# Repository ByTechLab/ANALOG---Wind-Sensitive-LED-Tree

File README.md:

<div align="center">
    
</div>

Wind sensitive LED tree project (analog circuit).

### Read more at BYTECHLAB:

<table style="width: 100%; border: none;" cellspacing="0" cellpadding="0" border="0">
  <tr>
    <td></td>
    <td>https://bytechlab.com/2019/02/led-tree/</td>
  </tr>
</table>

## License
Software \ Firmware:

Hardware \ Hardware design files \ Hardware documentation:

[![CC BY-NC-SA 4.0][cc-by-nc-sa-shield]][cc-by-nc-sa]

[Creative Commons Attribution-NonCommercial-ShareAlike 4.0 International License][cc-by-nc-sa].

[![CC BY-NC-SA 4.0][cc-by-nc-sa-image]][cc-by-nc-sa]

[cc-by-nc-sa]: http://creativecommons.org/licenses/by-nc-sa/4.0/
[cc-by-nc-sa-image]: https://licensebuttons.net/l/by-nc-sa/4.0/88x31.png
[cc-by-nc-sa-shield]: https://img.shields.io/badge/License-CC%20BY--NC--SA%204.0-lightgrey.svg

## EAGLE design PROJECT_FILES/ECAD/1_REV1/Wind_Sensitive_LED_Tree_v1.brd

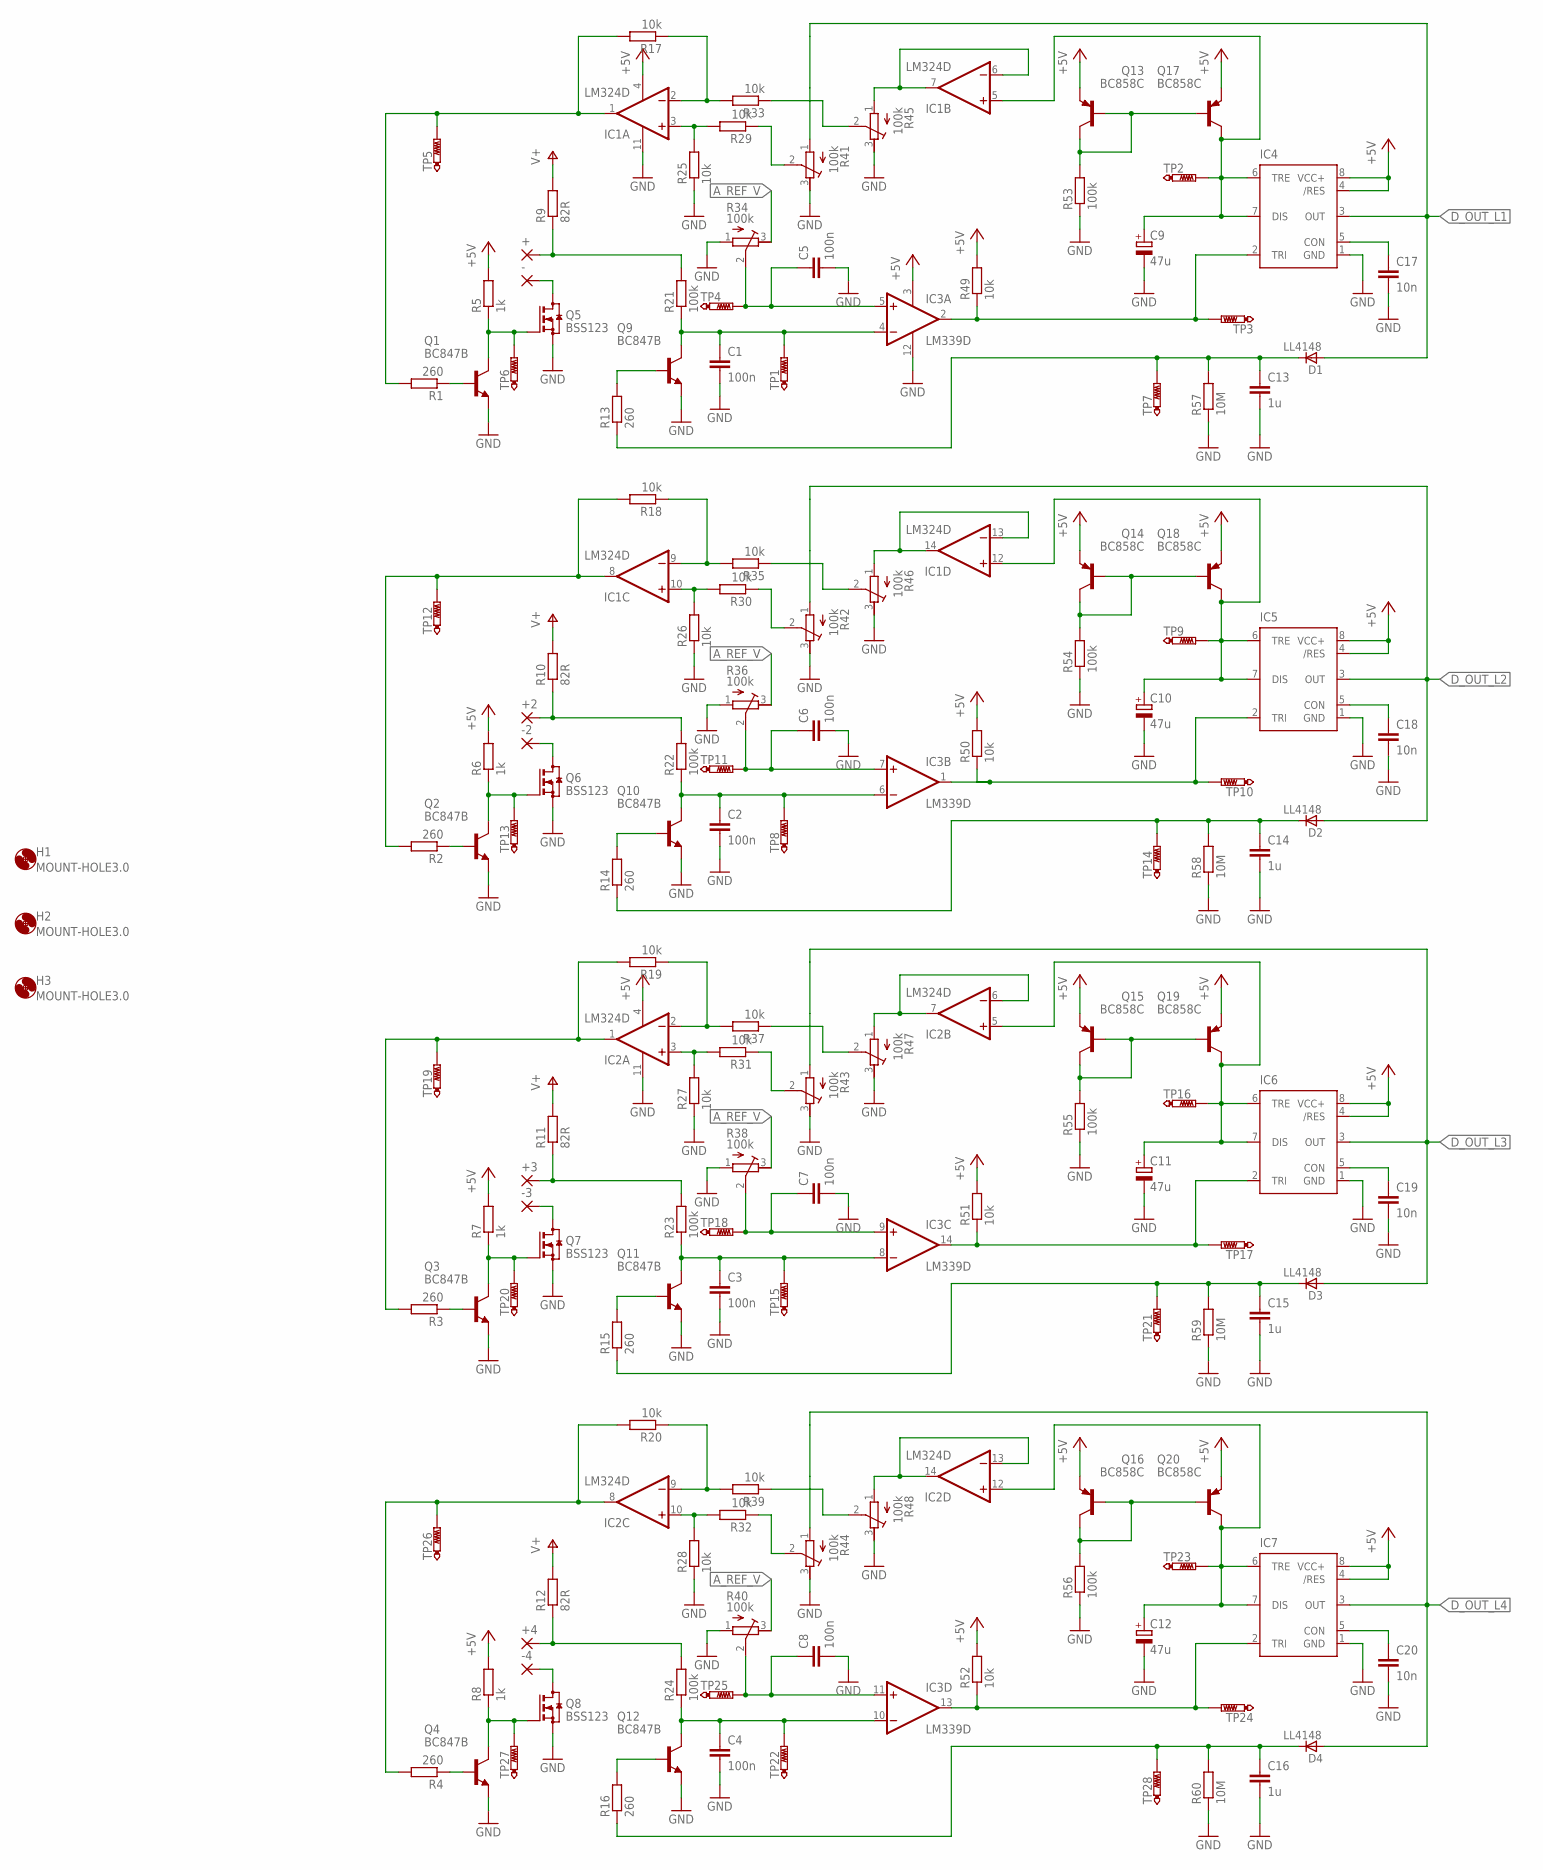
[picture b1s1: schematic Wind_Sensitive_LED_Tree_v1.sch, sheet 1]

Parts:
+, +2, +3, +4: SMD2; SMD1,27-2,54
-, -2, -3, -4: SMD2; SMD1,27-2,54
C1, C2, C3, C4, C5, C6, C7, C8: 100n; C1206
C9, C10, C11, C12: 47u; 153CLV-0605
C13, C14, C15, C16: 1u; C0805
C17, C18, C19, C20: 10n; C0805
D1, D2, D3, D4: LL4148; SOD80_DO213AA_MINIMELF
H1, H2, H3: MOUNT-HOLE3.0; 3,0
IC1, IC2: LM324D; SO14
IC3: LM339D; SO14
IC4, IC5, IC6, IC7: SPARKFUN-IC-SPECIAL-FUNCTION_555NE555_TSOP8; TSSOP8
Q1, Q2, Q3, Q4, Q9, Q10, Q11, Q12: BC847B; SOT23
Q5, Q6, Q7, Q8: BSS123; SOT23
Q13, Q14, Q15, Q16, Q17, Q18, Q19, Q20: BC858C; SOT23-BEC
R1, R2, R3, R4, R13, R14, R15, R16: 260; R0603
R5, R6, R7, R8: 1k; R0603
R9, R10, R11, R12: 82R; R0603
R17, R18, R19, R20, R25, R26, R27, R28, R29, R30, R31, R32, R33, R35, R37, R39, R49, R50, R51, R52: 10k; R0603
R21, R22, R23, R24, R53, R54, R55, R56: 100k; R0603
R34, R36, R38, R40, R41, R42, R43, R44, R45, R46, R47, R48: 100k; RTRIMCVR42A
R57, R58, R59, R60: 10M; R0603
TP1, TP2, TP3, TP4, TP5, TP6, TP7, TP8, TP9, TP10, TP11, TP12, TP13, TP14, TP15, TP16, TP17, TP18, TP19, TP20, TP21, TP22, TP23, TP24, TP25, TP26, TP27, TP28: PTR1B1,27; B1,27

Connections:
+5V: IC1.4 (V+), IC2.4 (V+), IC3.3 (V+), IC4.4 (/RES), IC4.8 (VCC+), IC5.4 (/RES), IC5.8 (VCC+), IC6.4 (/RES), IC6.8 (VCC+), IC7.4 (/RES), IC7.8 (VCC+), Q13.E, Q14.E, Q15.E, Q16.E, Q17.E, Q18.E, Q19.E, Q20.E, R5.2, R6.2, R7.2, R8.2, R49.2, R50.2, R51.2, R52.2; also elsewhere on the board
A_REF_V: R34.3 (E), R36.3 (E), R38.3 (E), R40.3 (E); also elsewhere on the board
D_OUT_L1: D1.A, IC4.3 (OUT), R41.1 (A); also elsewhere on the board
D_OUT_L2: D2.A, IC5.3 (OUT), R42.1 (A); also elsewhere on the board
D_OUT_L3: D3.A, IC6.3 (OUT), R43.1 (A); also elsewhere on the board
D_OUT_L4: D4.A, IC7.3 (OUT), R44.1 (A); also elsewhere on the board
GND: C1.2, C2.2, C3.2, C4.2, C5.2, C6.2, C7.2, C8.2, C9.-, C10.-, C11.-, C12.-, C13.2, C14.2, C15.2, C16.2, C17.2, C18.2, C19.2, C20.2, IC1.11 (V-), IC2.11 (V-), IC3.12 (GND), IC4.1 (GND), IC5.1 (GND), IC6.1 (GND), IC7.1 (GND), Q1.2 (E), Q2.2 (E), Q3.2 (E), Q4.2 (E), Q5.2 (S), Q6.2 (S), Q7.2 (S), Q8.2 (S), Q9.2 (E), Q10.2 (E), Q11.2 (E), Q12.2 (E), R25.1, R26.1, R27.1, R28.1, R34.1 (A), R36.1 (A), R38.1 (A), R40.1 (A), R41.3 (E), R42.3 (E), R43.3 (E), R44.3 (E), R45.3 (E), R46.3 (E), R47.3 (E), R48.3 (E), R53.1, R54.1, R55.1, R56.1, R57.1, R58.1, R59.1, R60.1; also elsewhere on the board
unnamed: -.1, Q5.3 (D)
unnamed: +.1, R9.1, R21.2
unnamed: Q1.3 (C), Q5.1 (G), R5.1, TP6.TP
unnamed: Q1.1 (B), R1.1
unnamed: IC1.1 (OUT), R1.2, R17.2, TP5.TP
unnamed: IC1.2 (-IN), R17.1, R33.2
unnamed: IC1.3 (+IN), R25.2, R29.2
unnamed: C1.1, IC3.4 (-IN), Q9.3 (C), R21.1, TP1.TP
unnamed: Q9.1 (B), R13.2
unnamed: IC3.2 (OUT), IC4.2 (TRI), R49.1, TP3.TP
unnamed: Q13.B, Q13.C, Q17.B, R53.2
unnamed: R29.1, R41.2 (S)
unnamed: R33.1, R45.2 (S)
unnamed: IC1.6 (-IN), IC1.7 (OUT), R45.1 (A)
unnamed: C9.+, IC1.5 (+IN), IC4.6 (TRE), IC4.7 (DIS), Q17.C, TP2.TP
unnamed: C13.1, D1.C, R13.1, R57.2, TP7.TP
unnamed: C17.1, IC4.5 (CON)
unnamed: C5.1, IC3.5 (+IN), R34.2 (S), TP4.TP
unnamed: -2.1, Q6.3 (D)
unnamed: +2.1, R10.1, R22.2
unnamed: Q2.3 (C), Q6.1 (G), R6.1, TP13.TP
unnamed: Q2.1 (B), R2.1
unnamed: IC1.8 (OUT), R2.2, R18.2, TP12.TP
unnamed: IC1.9 (-IN), R18.1, R35.2
unnamed: IC1.10 (+IN), R26.2, R30.2
unnamed: C2.1, IC3.6 (-IN), Q10.3 (C), R22.1, TP8.TP
unnamed: Q10.1 (B), R14.2
unnamed: IC3.1 (OUT), IC5.2 (TRI), R50.1, TP10.TP
unnamed: Q14.B, Q14.C, Q18.B, R54.2
unnamed: R30.1, R42.2 (S)
unnamed: R35.1, R46.2 (S)
unnamed: IC1.13 (-IN), IC1.14 (OUT), R46.1 (A)
unnamed: C10.+, IC1.12 (+IN), IC5.6 (TRE), IC5.7 (DIS), Q18.C, TP9.TP
unnamed: C18.1, IC5.5 (CON)
unnamed: C14.1, D2.C, R14.1, R58.2, TP14.TP
unnamed: C6.1, IC3.7 (+IN), R36.2 (S), TP11.TP
unnamed: -3.1, Q7.3 (D)
unnamed: +3.1, R11.1, R23.2
unnamed: Q3.3 (C), Q7.1 (G), R7.1, TP20.TP
unnamed: Q3.1 (B), R3.1
unnamed: IC2.1 (OUT), R3.2, R19.2, TP19.TP
unnamed: IC2.2 (-IN), R19.1, R37.2
unnamed: IC2.3 (+IN), R27.2, R31.2
unnamed: C3.1, IC3.8 (-IN), Q11.3 (C), R23.1, TP15.TP
unnamed: Q11.1 (B), R15.2
unnamed: IC3.14 (OUT), IC6.2 (TRI), R51.1, TP17.TP
unnamed: Q15.B, Q15.C, Q19.B, R55.2
unnamed: R31.1, R43.2 (S)
unnamed: R37.1, R47.2 (S)
unnamed: IC2.6 (-IN), IC2.7 (OUT), R47.1 (A)
unnamed: C11.+, IC2.5 (+IN), IC6.6 (TRE), IC6.7 (DIS), Q19.C, TP16.TP
unnamed: C19.1, IC6.5 (CON)
unnamed: C15.1, D3.C, R15.1, R59.2, TP21.TP
unnamed: C7.1, IC3.9 (+IN), R38.2 (S), TP18.TP
unnamed: -4.1, Q8.3 (D)
unnamed: +4.1, R12.1, R24.2
unnamed: Q4.3 (C), Q8.1 (G), R8.1, TP27.TP
unnamed: Q4.1 (B), R4.1
unnamed: IC2.8 (OUT), R4.2, R20.2, TP26.TP
unnamed: IC2.9 (-IN), R20.1, R39.2
unnamed: IC2.10 (+IN), R28.2, R32.2
unnamed: C4.1, IC3.10 (-IN), Q12.3 (C), R24.1, TP22.TP
unnamed: Q12.1 (B), R16.2
unnamed: IC3.13 (OUT), IC7.2 (TRI), R52.1, TP24.TP
unnamed: Q16.B, Q16.C, Q20.B, R56.2
unnamed: R32.1, R44.2 (S)
unnamed: R39.1, R48.2 (S)
unnamed: IC2.13 (-IN), IC2.14 (OUT), R48.1 (A)
unnamed: C12.+, IC2.12 (+IN), IC7.6 (TRE), IC7.7 (DIS), Q20.C, TP23.TP
unnamed: C20.1, IC7.5 (CON)
unnamed: C16.1, D4.C, R16.1, R60.2, TP28.TP
unnamed: C8.1, IC3.11 (+IN), R40.2 (S), TP25.TP
V+: R9.2, R10.2, R11.2, R12.2; also elsewhere on the board

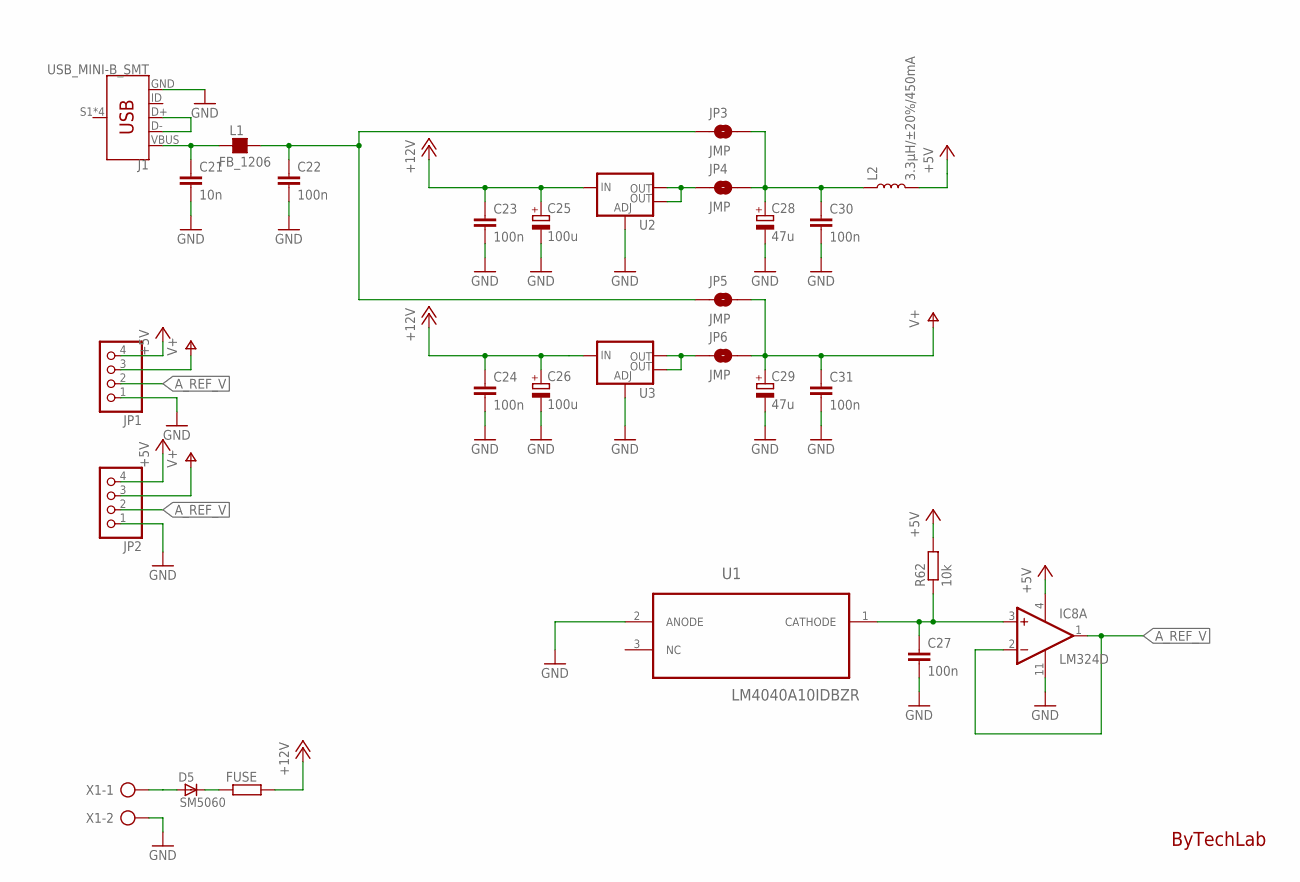
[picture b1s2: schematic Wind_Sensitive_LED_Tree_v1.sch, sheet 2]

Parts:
C21: 10n; C0805
C22, C23, C24, C27, C30, C31: 100n; C1206
C25, C26: 100u; 153CLV-0810
C28, C29: 47u; 153CLV-0605
D5: SM5060; MELF-MLL41_DO213AB
FUSE: R-EU_R1206; R1206
IC8: LM324D; SO14
J1: USB_MINI-B_SMT; USB-MINIB
JP1, JP2: PINHD-1X4; 1X04
JP3, JP4, JP5, JP6: JMP; SMT-JUMPER_2_NO_NO-SILK_ROUND
L1: FB_1206; L1206
L2: 3.3µH/±20%/450mA; 0805
R62: 10k; R0603
U1: LM4040A10IDBZR; SOT95P237X112-3N
U2, U3: V_REG_LM1117SOT223; SOT223
X1: AK300/2

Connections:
+5V: IC8.4 (V+), JP1.4, JP2.4, L2.2, R62.2; also elsewhere on the board
+12V: C23.1, C24.1, C25.+, C26.+, FUSE.2, U2.3 (IN), U3.3 (IN); also elsewhere on the board
A_REF_V: IC8.1 (OUT), IC8.2 (-IN), JP1.2, JP2.2; also elsewhere on the board
GND: C21.2, C22.2, C23.2, C24.2, C25.-, C26.-, C27.2, C28.-, C29.-, C30.2, C31.2, IC8.11 (V-), J1.GND, JP1.1, JP2.1, U1.2 (ANODE), U2.1 (ADJ), U3.1 (ADJ), X1.2; also elsewhere on the board
unnamed: C21.1, J1.VBUS, L1.1
unnamed: C27.1, IC8.3 (+IN), R62.1, U1.1 (CATHODE)
unnamed: C28.+, C30.1, JP3.2, JP4.2, L2.1
unnamed: C22.1, JP3.1, JP5.1, L1.2
unnamed: J1.D+, J1.D-
unnamed: JP4.1, U2.2 (OUT), U2.4 (OUT)
unnamed: JP6.1, U3.2 (OUT), U3.4 (OUT)
unnamed: D5.A, X1.1
unnamed: D5.C, FUSE.1
V+: C29.+, C31.1, JP1.3, JP2.3, JP5.2, JP6.2; also elsewhere on the board

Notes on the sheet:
ByTechLab

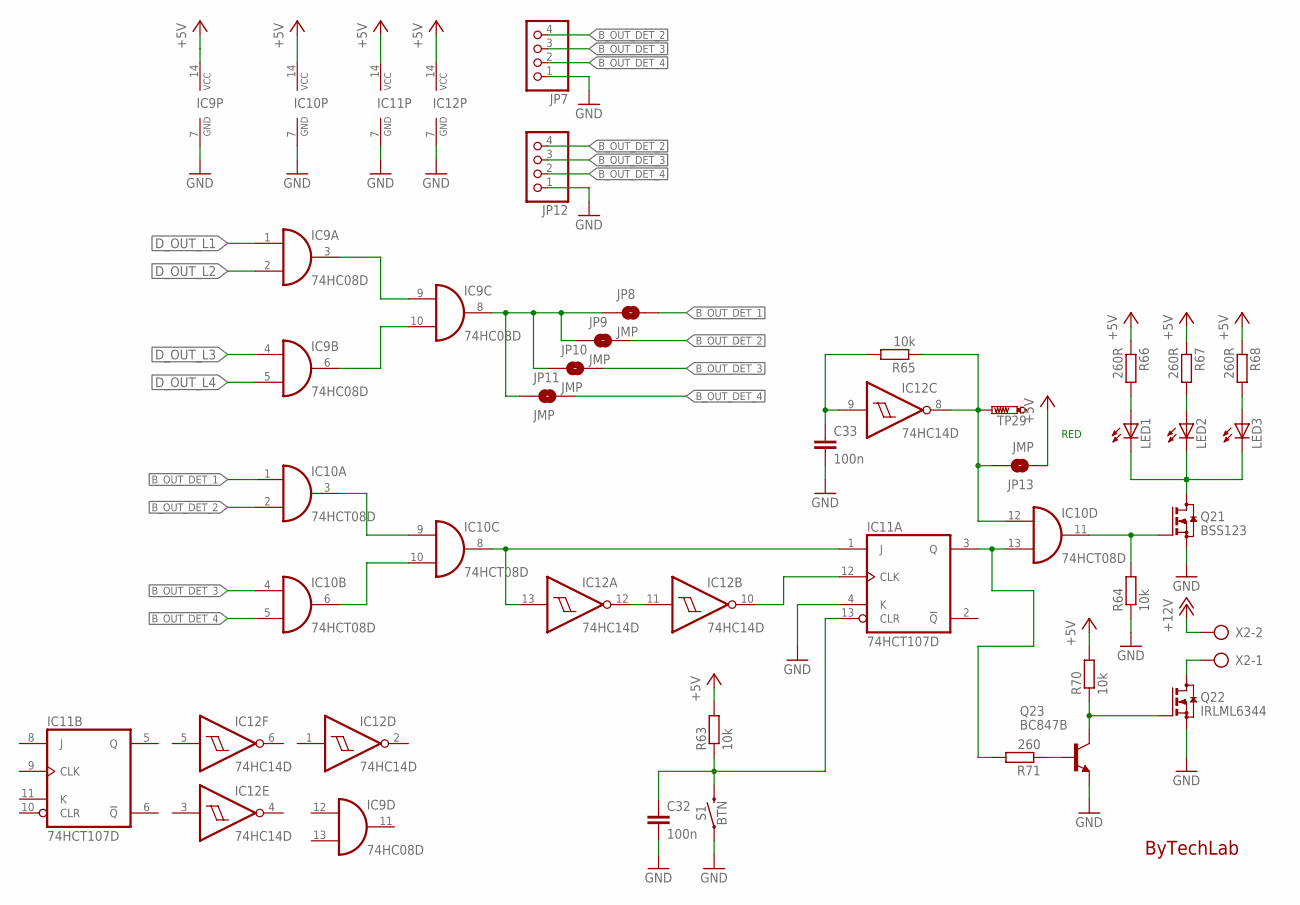
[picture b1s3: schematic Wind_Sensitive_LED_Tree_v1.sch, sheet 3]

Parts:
C32, C33: 100n; C1206
IC9: 74HC08D; SO14
IC10: 74HCT08D; SO14
IC11: 74HCT107D; SO14
IC12: 74HC14D; SO14
JP7, JP12: PINHD-1X4; 1X04
JP8, JP9, JP10, JP11, JP13: JMP; SMT-JUMPER_2_NO_SILK
LED1, LED2, LED3: LEDCHIPLED_0805; CHIPLED_0805
Q21: BSS123; SOT23
Q22: IRLML6344; SOT23
Q23: BC847B; SOT23
R63, R64, R65, R70: 10k; R0603
R66, R67, R68: 260R; R0603
R71: 260; R0603
S1: BTN; TACTILE_SWITCH_SMD_6.0X3.5MM
TP29: PTR1B1,27; B1,27
X2: AK300/2

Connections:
+5V: IC9.14 (VCC), IC10.14 (VCC), IC11.14 (VCC), IC12.14 (VCC), JP13.1, R63.2, R66.1, R67.1, R68.1, R70.2; also elsewhere on the board
+12V: X2.2; also elsewhere on the board
B_OUT_DET_1: IC10.1 (I0), JP8.2
B_OUT_DET_2: IC10.2 (I1), JP7.4, JP9.2, JP12.4
B_OUT_DET_3: IC10.4 (I0), JP7.3, JP10.2, JP12.3
B_OUT_DET_4: IC10.5 (I1), JP7.2, JP11.2, JP12.2
D_OUT_L1: IC9.1 (I0); also elsewhere on the board
D_OUT_L2: IC9.2 (I1); also elsewhere on the board
D_OUT_L3: IC9.4 (I0); also elsewhere on the board
D_OUT_L4: IC9.5 (I1); also elsewhere on the board
GND: C32.2, C33.2, IC9.7 (GND), IC10.7 (GND), IC11.4 (K), IC11.7 (GND), IC12.7 (GND), JP7.1, JP12.1, Q21.2 (S), Q22.2 (S), Q23.2 (E), R64.1, S1.1; also elsewhere on the board
unnamed: IC9.3 (O), IC9.9 (I0)
unnamed: IC9.6 (O), IC9.10 (I1)
unnamed: IC9.8 (O), JP8.1, JP9.1, JP10.1, JP11.1
unnamed: IC10.3 (O), IC10.9 (I0)
unnamed: IC10.6 (O), IC10.10 (I1)
unnamed: IC12.11 (I), IC12.12 (O)
unnamed: IC10.8 (O), IC11.1 (J), IC12.13 (I)
unnamed: IC11.12 (CLK), IC12.10 (O)
unnamed: C32.1, IC11.13 (CLR), R63.1, S1.2
unnamed: IC10.11 (O), Q21.1 (G), R64.2
unnamed: Q22.3 (D), X2.1
unnamed: C33.1, IC12.9 (I), R65.2
unnamed: IC10.12 (I0), IC12.8 (O), JP13.2, R65.1, TP29.TP
unnamed: LED1.C, LED2.C, LED3.C, Q21.3 (D)
unnamed: LED1.A, R66.2
unnamed: LED2.A, R67.2
unnamed: LED3.A, R68.2
unnamed: IC10.13 (I1), IC11.3 (Q), R71.2
unnamed: Q22.1 (G), Q23.3 (C), R70.1
unnamed: Q23.1 (B), R71.1

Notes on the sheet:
RED
ByTechLab

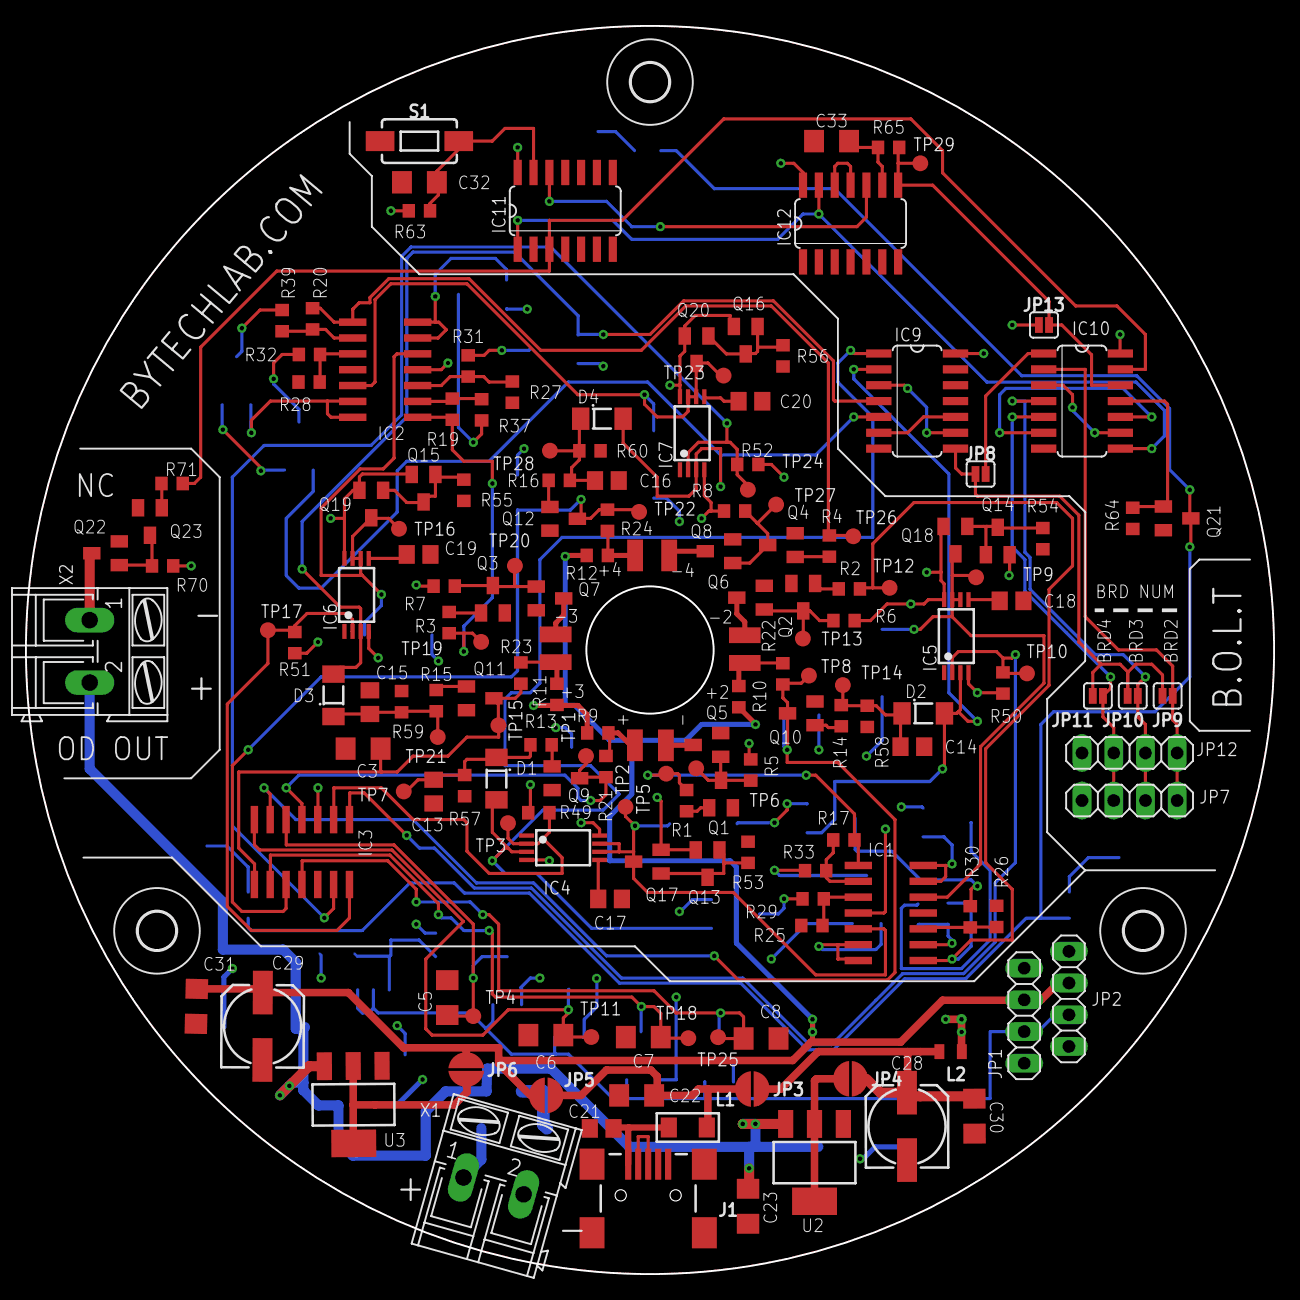
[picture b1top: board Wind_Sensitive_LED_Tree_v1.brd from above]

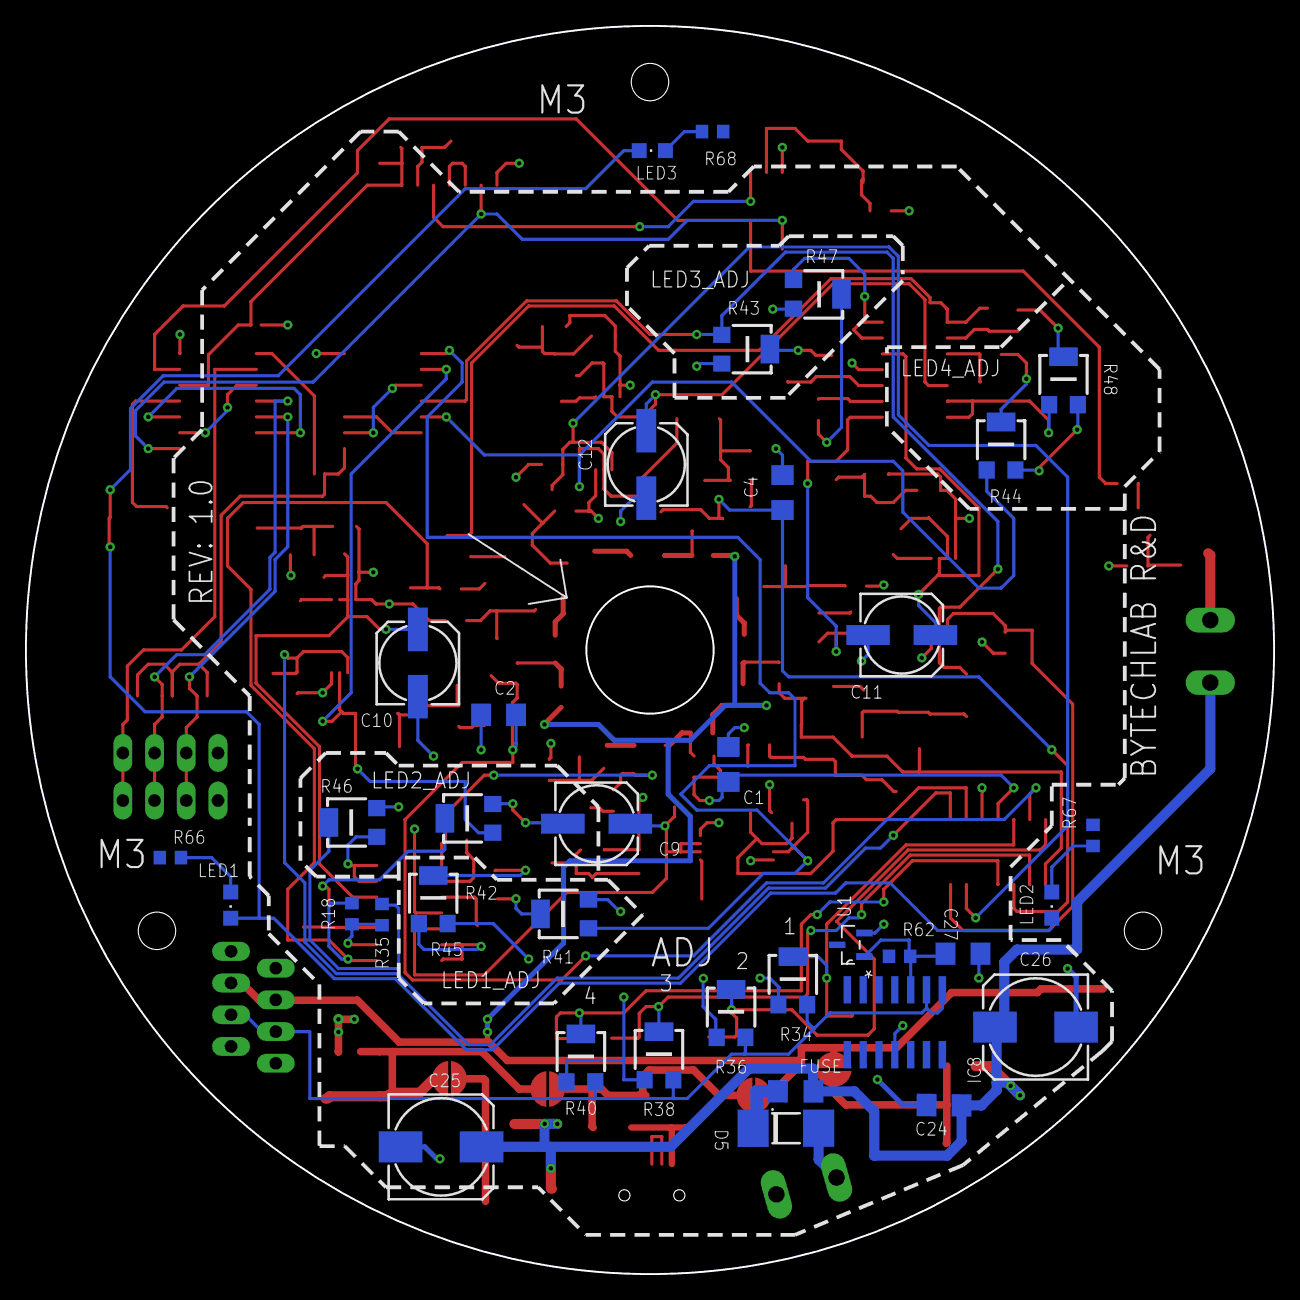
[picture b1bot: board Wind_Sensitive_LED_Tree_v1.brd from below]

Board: 2 copper layers, 100.0 x 100.0 mm, 208 parts (36 on the bottom side), 114 nets.

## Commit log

2024-11-09 Upload project files

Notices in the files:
parts and their libraries:
SparkFun-IC-Power: Licensing: Creative Commons ShareAlike 4.0 International - https://creativecommons.org/licenses/by-sa/4.0
rc-master-smd: Copyright (C) 2007, Bob Starr
